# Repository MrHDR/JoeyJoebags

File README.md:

# JoeyJoebags
Tools, firmware and software for the JoeyJoebags

**Please note that this section exists to help users fix broken devices they have purchased from BennVenn, no support will be provided beyond this readme**

### Firmware Flashing

#### Software Flashing (Arduino ide)

**Required Software:**
- [Arduino IDE](https://www.arduino.cc/en/main/software)
- [Arduino_STM32](https://github.com/rogerclarkmelbourne/Arduino_STM32/wiki/Installation)

**Flashing the firmware:**
1. Open "JoeyBootloader.ino" in the Arduino IDE
2. Connect the maple mini over usb
3. Under "Tools" select the following options:
```
Board: "Maple Mini"
Bootloader version: "Original (17k RAM, 108k Flash)"
CPU Speed(MHz): "48MHz (Slow - with USB)"
Optimize: "Smallest (default)"
Port: COM# (Maple Mini)" ##Where # is the COM number of your device
```

4. Click Upload and open the serial monitor
5. That's it, you're done

[Video Guide](https://www.youtube.com/watch?v=m3snxbclFE0)

#### Hardware Flashing (If the maple mini does not have the default bootloader)

**Required Software:**
- [JoeyFirmwareTool](https://github.com/HDR/JoeyJoebags/releases)
- [stm32flash](https://sourceforge.net/projects/stm32flash/)

**Required Tools:**
- CP2102 (or any other device that can be used for flashing)

#### Maple Mini

**Pinout:**

| Maple Mini | CP2102 |
|------------|------------|
| GND | GND |
| 25(RX1) | TXD |
| 26(TX1) | RXD |
| VIN | 5V |

| Maple Mini | Maple Mini |
|------------|------------|
| VCC | BUT(boot0) |
| GND | boot1 |

Connect everything according to the above pinout (boot1 and boot0 are not needed if you set the maple mini to flash mode using the buttons) 

**Flashing the firmware:**
1. Drop a .ben file onto "JoeyFirmwareTool.exe", this will produce a file called "JoeyFirmware.bin"
2. Find out what com port your flashing tool is (for this example i will be using COM8)
3. open commandline and navigate to your stm32flash folder
4. run `stm32flash -w JoeyFirmware.bin -v -g 0x0 COM8` and your maple mini will be flashed.
5. That's it, you're done!

#### STM32F103C8T6

**Pinout:**

| STM32F103C8T6 | CP2102 |
|------------|------------|
| Pin 47 | GND |
| Pin 30 | TXD |
| Pin 31 | RXD |
| Pin 48 | 3.3V |
| Pin 44 | 3.3V |
| Pin 20 | GND |

**Flashing the firmware:**
1. Drop a .ben file onto "JoeyFirmwareTool.exe", this will produce a file called "JoeyFirmware.bin"
2. Find out what com port your flashing tool is (for this example i will be using COM8)
3. open commandline and navigate to your stm32flash folder
4. run `stm32flash -w JoeyFirmware.bin -v -g 0x0 COM8` and your STM32F103C8T6 will be flashed.
5. That's it, you're done!

# Custom Signed Driver

Unzip the "JoeyJoebags_Signed_Driver.zip" file and right click "Install Driver.bat" and run is as an admin, no reboots or disabling driver signature enforecement needed.

# Compiling/Decompiling Windows Software Binaries

### Compiling
Run ```python -m py2exe JoeyJoebags.py``` to compile windows binaries

Alternatively you can use this script
```
from distutils.core import setup
import py2exe, sys

sys.argv.append('py2exe')

setup(
        options = {
                    'py2exe': {'bundle_files': 2,
                               'compressed': True
                              }
                  },
        console = [{
                    'script': "JoeyJoebags.py",
					'icon_resources': [(0, 'favicon.ico')]
                  }],
        zipfile = None,
)
```

### Requirements
```
Python 3.4
PyUSB
py2exe
```

### Installing Requirements
1. Download & Install Python 3.4 64bit from https://www.python.org/downloads/windows/
2. open cmd as admin and type ```python -m pip install PyUSB``` & ```python -m pip install py2exe```

### Decompiling
To decompile the binary you will need python_exe_unpack.py from https://github.com/countercept/python-exe-unpacker just follow the instructions in the readme, to decompile the exe use ```python python_exe_unpack.py -i JoeyJoebags.exe```

If you experience any issues with installing PyCrypto for the decompiler, install this https://github.com/axper/python3-pycrypto-windows-installer

### Requirements
```
Python 3.4
pefile
unpy2exe
uncompyle6
xdis
pycrypto
configparser
```

### Installing Requirements
1. Download & Install Python 3.4 64bit from https://www.python.org/downloads/windows/
2. Download https://github.com/countercept/python-exe-unpacker
3. open cmd as admin in the python-exe-unpacker folder and type ```python -m pip install -r requirements.txt```

## Custom Software Additions

- Fixes dumping 32MB repros like the DV15 & PPP08

- Dumping / Flashing completion percentage

- Progress is now shown on a single line

- Removed dotted lines at the top of all menu entries

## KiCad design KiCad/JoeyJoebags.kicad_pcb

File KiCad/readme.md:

# Joey Gen 3 Replacement PCBs

**Handles voltages improperly, i recommend not using them with GBA games**

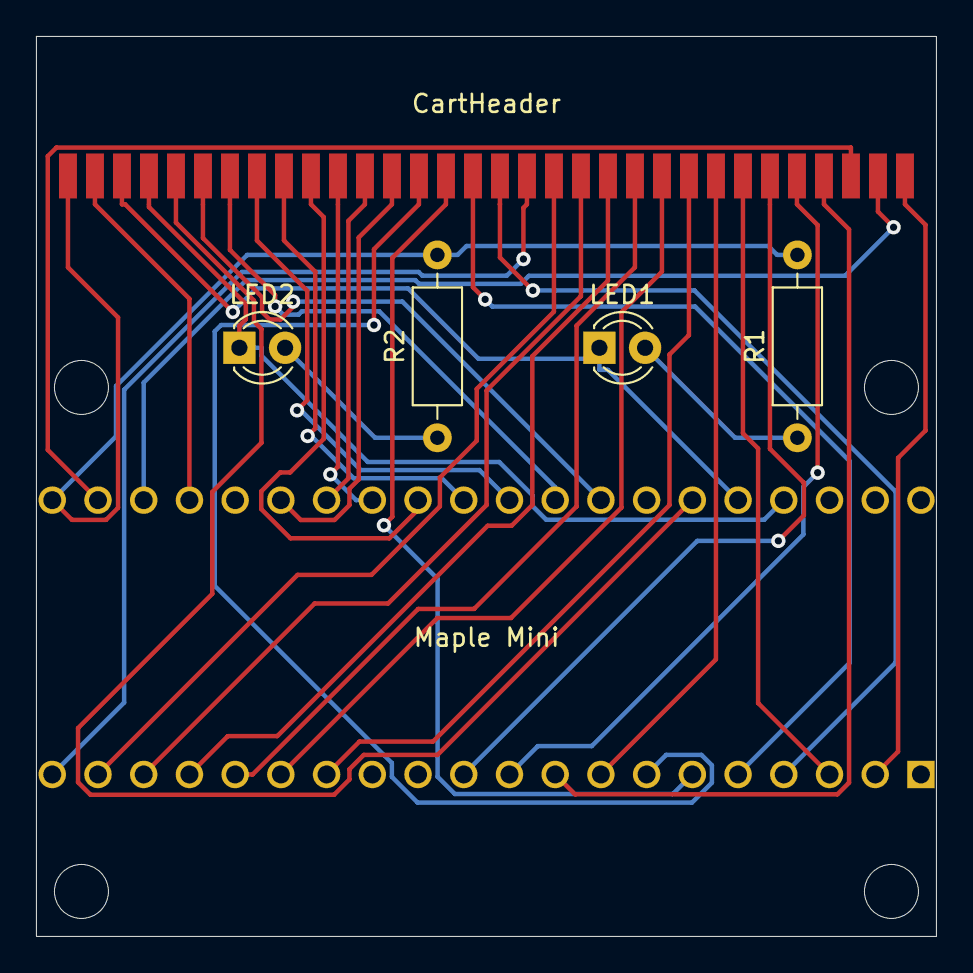
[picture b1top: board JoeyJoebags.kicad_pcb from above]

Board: 2 copper layers, 50.0 x 50.0 mm, 6 parts (1 on the bottom side), 34 nets.

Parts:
CartHeader: CartBus; DSL_Cartridge_Reader_Micro
LED1, LED2: LED; LED_D3.0mm
Maple Mini: Maple_Mini_Fixed
R1, R2: R; R_Axial_DIN0207_L6.3mm_D2.5mm_P10.16mm_Horizontal

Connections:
D2-boot1: CartHeader.2, Maple Mini.24
D32-boot0: CartHeader.26, Maple Mini.3
GND: CartHeader.32, Maple Mini.2
M0: CartHeader.30, Maple Mini.22
M1: CartHeader.31, Maple Mini.23
M4: CartHeader.13, Maple Mini.26
M5: CartHeader.12, Maple Mini.27
M6: CartHeader.11, Maple Mini.28
M7: CartHeader.10, Maple Mini.29
M8: CartHeader.9, Maple Mini.30
M9: CartHeader.8, Maple Mini.31
M10: CartHeader.7, Maple Mini.32
M11: CartHeader.6, Maple Mini.33
M12: CartHeader.5, Maple Mini.35
M13: CartHeader.3, LED1.1, Maple Mini.36
M14: CartHeader.4, LED2.1, Maple Mini.37
M15: CartHeader.17, Maple Mini.4
M16: CartHeader.16, Maple Mini.5
M17: CartHeader.15, Maple Mini.6
M18: CartHeader.14, Maple Mini.7
M19: CartHeader.25, Maple Mini.8
M20: CartHeader.29, Maple Mini.9
M21: CartHeader.28, Maple Mini.10
M22: CartHeader.27, Maple Mini.11
M25: CartHeader.24, Maple Mini.14
M26: CartHeader.23, Maple Mini.15
M27: CartHeader.22, Maple Mini.16
M28: CartHeader.21, Maple Mini.17
M29: CartHeader.20, Maple Mini.18
M30: CartHeader.19, Maple Mini.19
M31: CartHeader.18, Maple Mini.20
unnamed: LED1.2, R1.1
unnamed: LED2.2, R2.1
VIN: CartHeader.1, Maple Mini.21, R1.2, R2.2

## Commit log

2018-11-08 Add 3.17
2018-11-08 Add tons of firmwares and source code
2020-01-05 Add signed driver for easy installs
2020-01-23 Add pcb
2020-01-23 Rename index.md to readme.md
2020-01-23 add images
2020-01-23 Update images
2020-02-03 Add JoeyFirmTool and Gen3 Mini
2020-02-03 Cleanup readme and add flashing guide
2020-02-12 Fix broken footprint for maple mini
2020-03-24 Add software flashing instructions
2020-07-02 Rename Circuit board to KiCad
2020-07-09 Removed board files, as people were abusing them
    Owners of the Joey Gen3 can still message me if they have a broken board.
2021-03-24 re-add kicad files
    Since the product is no longer available and will no longer be updated by Benn, i have decided to re-release the kicad files.
